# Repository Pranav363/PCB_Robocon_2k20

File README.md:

# PCB_Robocon_2k20
The ABU Asia-Pacific Robot Contest (ABU Robocon) is an Asian-Oceanian college robot competition.
In the competition, robots compete to complete a task within a set period of time.

Attached files are PCB designs used by TEAM VULCANS in Robocon2020 competition.
This repository contains .brd & .sch file desgined in EAGLE software.

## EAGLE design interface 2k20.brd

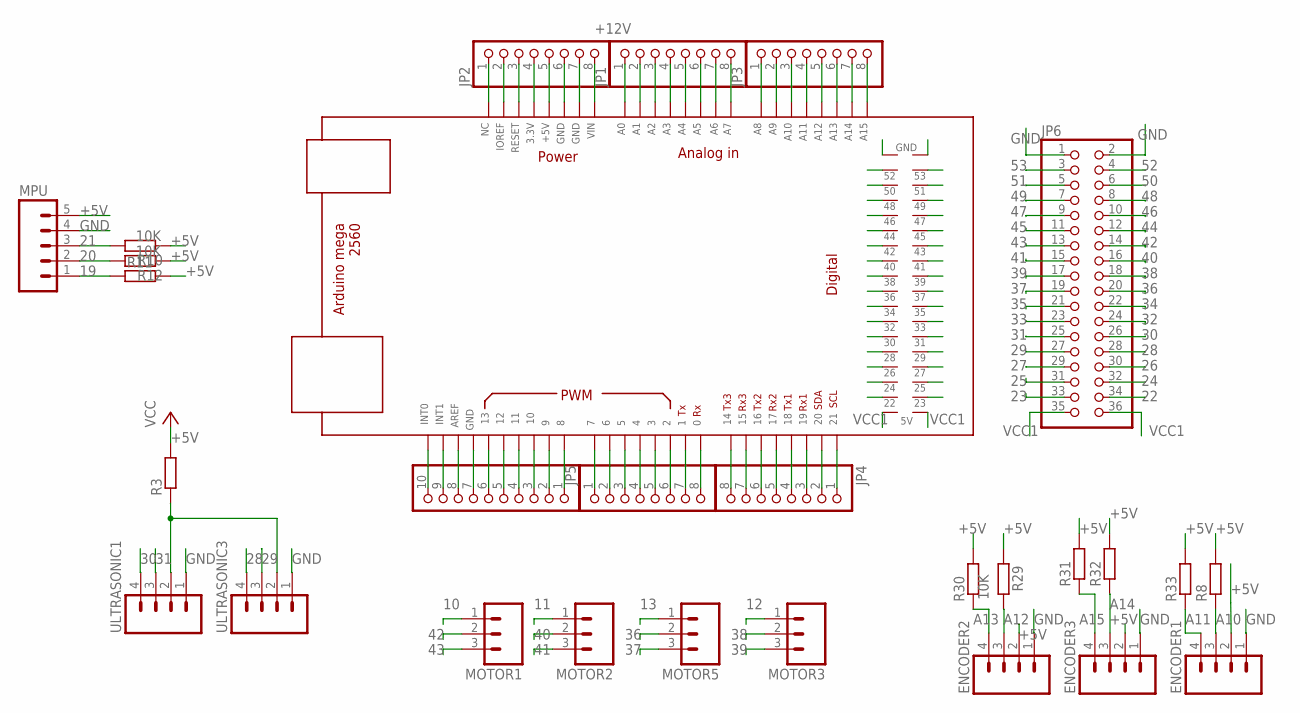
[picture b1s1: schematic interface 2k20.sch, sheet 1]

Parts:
ENCODER1, ENCODER2, ENCODER3: ULTRASONIC; MOLEX-1X4
JP1, JP2, JP3, JP4, JP5: PINHD-1X8; 1X08
JP6: PINHD-2X18; 2X18
MOTOR1, MOTOR2, MOTOR3, MOTOR5: M03POLAR; MOLEX-1X3@1
MPU: M05; 05P
PWMH1: pwm; 1X10
R3, R8, R11, R29, R31, R32, R33: R-EU_M0805; M0805
R10, R12, R30: 10K; M0805
U$1: MEGA_DEVICE; MEGABOX
ULTRASONIC1, ULTRASONIC3: ULTRASONIC; MOLEX-1X4

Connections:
0: JP5.8, U$1.0
1: JP5.7, U$1.1
2: JP5.6, U$1.2
3: JP5.5, U$1.3
3.3V: JP2.4, U$1.3V3
4: JP5.4, U$1.4
5: JP5.3, U$1.5
6: JP5.2, U$1.6
7: JP5.1, U$1.7
8: PWMH1.1, U$1.8
9: PWMH1.2, U$1.9
10: MOTOR1.1, PWMH1.3, U$1.10
11: MOTOR2.1, PWMH1.4, U$1.11
12: MOTOR3.1, PWMH1.5, U$1.12
13: MOTOR5.1, PWMH1.6, U$1.13
14: JP4.8, U$1.14
15: JP4.7, U$1.15
16: JP4.6, U$1.16
17: JP4.5, U$1.17
18: JP4.4, U$1.18
19: JP4.3, MPU.1, R11.2, U$1.19
20: JP4.2, MPU.2, R12.2, U$1.20
21: JP4.1, MPU.3, R10.2, U$1.21
22: JP6.34, U$1.22; also elsewhere on the board
23: JP6.33, U$1.23; also elsewhere on the board
24: JP6.32, U$1.24; also elsewhere on the board
25: JP6.31, U$1.25; also elsewhere on the board
26: JP6.30, U$1.26
27: JP6.29, U$1.27
28: JP6.28, U$1.28, ULTRASONIC3.4
29: JP6.27, U$1.29, ULTRASONIC3.3
30: JP6.26, U$1.30, ULTRASONIC1.4
31: JP6.25, U$1.31, ULTRASONIC1.3
32: JP6.24, U$1.32
33: JP6.23, U$1.33
34: JP6.22, U$1.34
35: JP6.21, U$1.35
36: JP6.20, MOTOR5.2, U$1.36
37: JP6.19, MOTOR5.3, U$1.37
38: JP6.18, MOTOR3.2, U$1.38
39: JP6.17, MOTOR3.3, U$1.39
40: JP6.16, MOTOR2.2, U$1.40
41: JP6.15, MOTOR2.3, U$1.41
42: JP6.14, MOTOR1.2, U$1.42
43: JP6.13, MOTOR1.3, U$1.43
44: JP6.12, U$1.44
45: JP6.11, U$1.45; also elsewhere on the board
46: JP6.10, U$1.46; also elsewhere on the board
47: JP6.9, U$1.47; also elsewhere on the board
48: JP6.8, U$1.48; also elsewhere on the board
49: JP6.7, U$1.49; also elsewhere on the board
50: JP6.6, U$1.50; also elsewhere on the board
51: JP6.5, U$1.51; also elsewhere on the board
52: JP6.4, U$1.52; also elsewhere on the board
53: JP6.3, U$1.53; also elsewhere on the board
+5V: ENCODER1.2, ENCODER2.2, ENCODER3.2, MPU.5, R3.2, R8.2, R10.1, R11.1, R12.1, R29.2, R30.2, R31.2, R32.2, R33.2; also elsewhere on the board
+12V: JP2.8, U$1.VIN; also elsewhere on the board
A0: JP1.1, U$1.A0
A1: JP1.2, U$1.A1
A2: JP1.3, U$1.A2
A3: JP1.4, U$1.A3
A4: JP1.5, U$1.A4
A5: JP1.6, U$1.A5
A6: JP1.7, U$1.A6
A7: JP1.8, U$1.A7
A8: JP3.1, U$1.A8
A9: JP3.2, U$1.A9
A10: ENCODER1.3, JP3.3, R8.1, U$1.A10
A11: ENCODER1.4, JP3.4, R33.1, U$1.A11
A12: ENCODER2.3, JP3.5, R29.1, U$1.A12
A13: ENCODER2.4, JP3.6, R30.1, U$1.A13
A14: ENCODER3.3, JP3.7, R32.1, U$1.A14
A15: ENCODER3.4, JP3.8, R31.1, U$1.A15
AREF: PWMH1.8, U$1.AREF
GND: ENCODER1.1, ENCODER2.1, ENCODER3.1, JP2.6, JP2.7, JP6.1, JP6.2, MPU.4, PWMH1.7, U$1.GND@1 (GND), U$1.GND@2 (GND), U$1.GND@3 (GND), U$1.GND@4 (GND), U$1.GND@5 (GND), ULTRASONIC1.1, ULTRASONIC3.1; also elsewhere on the board
INT0: PWMH1.10, U$1.INT2
INT1: PWMH1.9, U$1.INT1
IOREF: JP2.2, U$1.IOREF
unnamed: R3.1, ULTRASONIC1.2, ULTRASONIC3.2
NC: JP2.1, U$1.NC
RESET: JP2.3, U$1.RESET; also elsewhere on the board
VCC: JP2.5, U$1.5V; also elsewhere on the board
VCC1: JP6.35, JP6.36, U$1.5V@1 (5V), U$1.5V@2 (5V)

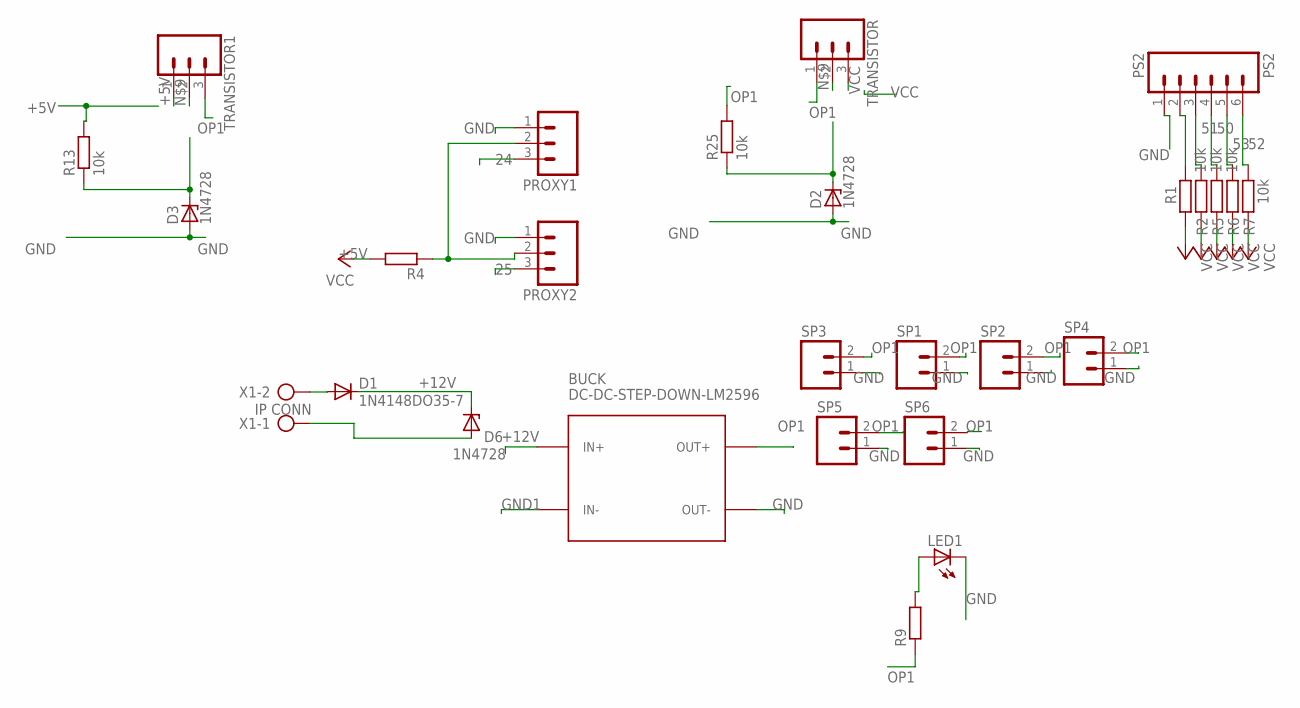
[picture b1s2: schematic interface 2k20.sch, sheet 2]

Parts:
BUCK: DC-DC-STEP-DOWN-LM2596
D1: 1N4148DO35-7; DO35-7
D2, D3, D6: 1N4728; DO41Z10
LED1: LEDCHIPLED_0805; CHIPLED_0805
PROXY1, PROXY2: M03POLAR; MOLEX-1X3@1
PS2: PS2; MOLEX-1X6
R1, R4: R-EU_M0805; M0805
R2, R5, R6, R7, R13, R25: 10k; M0805
R9: 500; M0805
SP1, SP2, SP3, SP4, SP5, SP6: M02; 02P
TRANSISTOR, TRANSISTOR1: CONN_03LOCK; 1X03_LOCK
X1: IP CONN; AK300/2

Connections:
24: PROXY1.3; also elsewhere on the board
25: PROXY2.3; also elsewhere on the board
50: PS2.4, R5.2; also elsewhere on the board
51: PS2.3, R2.2; also elsewhere on the board
52: PS2.6, R7.2; also elsewhere on the board
53: PS2.5, R6.2; also elsewhere on the board
+5V: R1.1, R2.1, R4.2, R5.1, R6.1, R7.1, R13.2, TRANSISTOR1.1; also elsewhere on the board
+12V: BUCK.IN+, D1.C, D6.C; also elsewhere on the board
GND: BUCK.OUT-, D2.A, D3.A, LED1.C, PROXY1.1, PROXY2.1, PS2.1, SP1.1, SP2.1, SP3.1, SP4.1, SP5.1, SP6.1; also elsewhere on the board
GND1: BUCK.IN-, D6.A, X1.1
unnamed: LED1.A, R9.2
unnamed: D1.A, X1.2
unnamed: PROXY1.2, PROXY2.2, R4.1
unnamed: D2.C, D3.C, R13.1, R25.1, TRANSISTOR.2, TRANSISTOR1.2
unnamed: PS2.2, R1.2
OP1: BUCK.OUT+, R9.1, R25.2, SP1.2, SP2.2, SP3.2, SP4.2, SP5.2, SP6.2, TRANSISTOR.1, TRANSISTOR1.3
VCC: TRANSISTOR.3; also elsewhere on the board

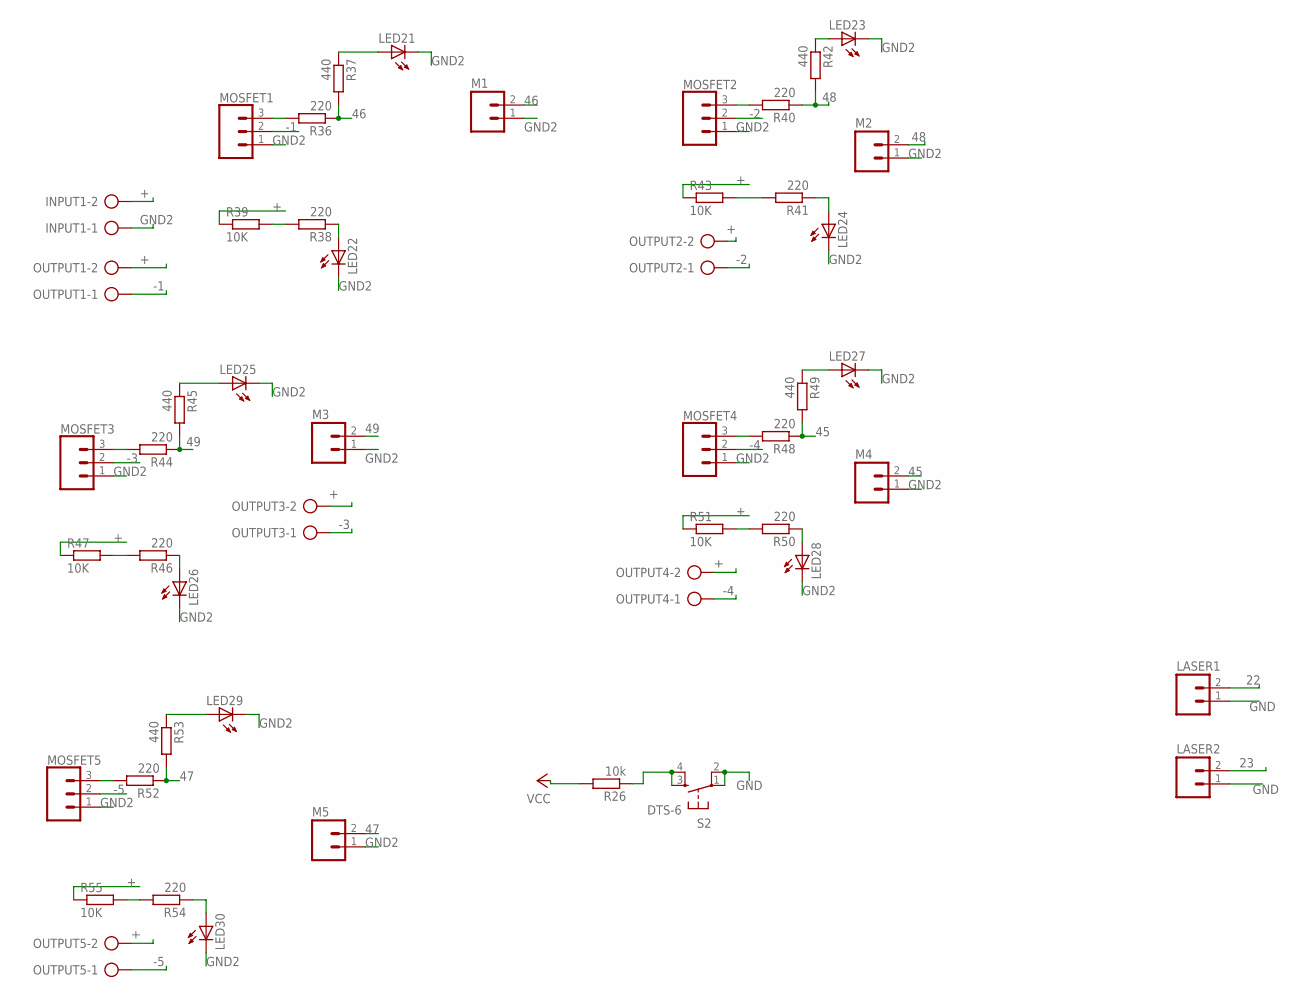
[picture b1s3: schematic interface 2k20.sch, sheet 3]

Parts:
INPUT1: AK300/2
LASER1, LASER2: M02; 02P
LED21, LED22, LED23, LED24, LED25, LED26, LED27, LED28, LED29, LED30: LEDCHIPLED_0805; CHIPLED_0805
M1, M2, M3, M4, M5: M02; 02P
MOSFET1, MOSFET2, MOSFET3, MOSFET4, MOSFET5: CONN_03LOCK; 1X03_LOCK
OUTPUT1, OUTPUT2, OUTPUT3, OUTPUT4, OUTPUT5: AK300/2
R26: 10k; M0805
R36, R38, R40, R41, R44, R46, R48, R50, R52, R54: 220; M0805
R37, R42, R45, R49, R53: 440; M0805
R39, R43, R47, R51, R55: 10K; R0805
S2: DTS-6

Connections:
22: LASER1.2; also elsewhere on the board
23: LASER2.2; also elsewhere on the board
45: M4.2, R48.1, R49.2; also elsewhere on the board
46: M1.2, R36.1, R37.2; also elsewhere on the board
47: M5.2, R52.1, R53.2; also elsewhere on the board
48: M2.2, R40.1, R42.2; also elsewhere on the board
49: M3.2, R44.1, R45.2; also elsewhere on the board
+: INPUT1.2, OUTPUT1.2, OUTPUT2.2, OUTPUT3.2, OUTPUT4.2, OUTPUT5.2, R39.1, R43.1, R47.1, R51.1, R55.1
+5V: R26.2; also elsewhere on the board
-1: MOSFET1.2, OUTPUT1.1
-2: MOSFET2.2, OUTPUT2.1
-3: MOSFET3.2, OUTPUT3.1
-4: MOSFET4.2, OUTPUT4.1
-5: MOSFET5.2, OUTPUT5.1
GND: LASER1.1, LASER2.1, S2.1, S2.2; also elsewhere on the board
GND2: INPUT1.1, LED21.C, LED22.C, LED23.C, LED24.C, LED25.C, LED26.C, LED27.C, LED28.C, LED29.C, LED30.C, M1.1, M2.1, M3.1, M4.1, M5.1, MOSFET1.1, MOSFET2.1, MOSFET3.1, MOSFET4.1, MOSFET5.1
unnamed: MOSFET1.3, R36.2
unnamed: LED21.A, R37.1
unnamed: LED22.A, R38.1
unnamed: R38.2, R39.2
unnamed: MOSFET2.3, R40.2
unnamed: LED23.A, R42.1
unnamed: R41.2, R43.2
unnamed: LED24.A, R41.1
unnamed: MOSFET3.3, R44.2
unnamed: LED25.A, R45.1
unnamed: LED26.A, R46.1
unnamed: R46.2, R47.2
unnamed: MOSFET4.3, R48.2
unnamed: LED27.A, R49.1
unnamed: LED28.A, R50.1
unnamed: R50.2, R51.2
unnamed: LED29.A, R53.1
unnamed: MOSFET5.3, R52.2
unnamed: R54.2, R55.2
unnamed: LED30.A, R54.1
RESET: R26.1, S2.3, S2.4; also elsewhere on the board

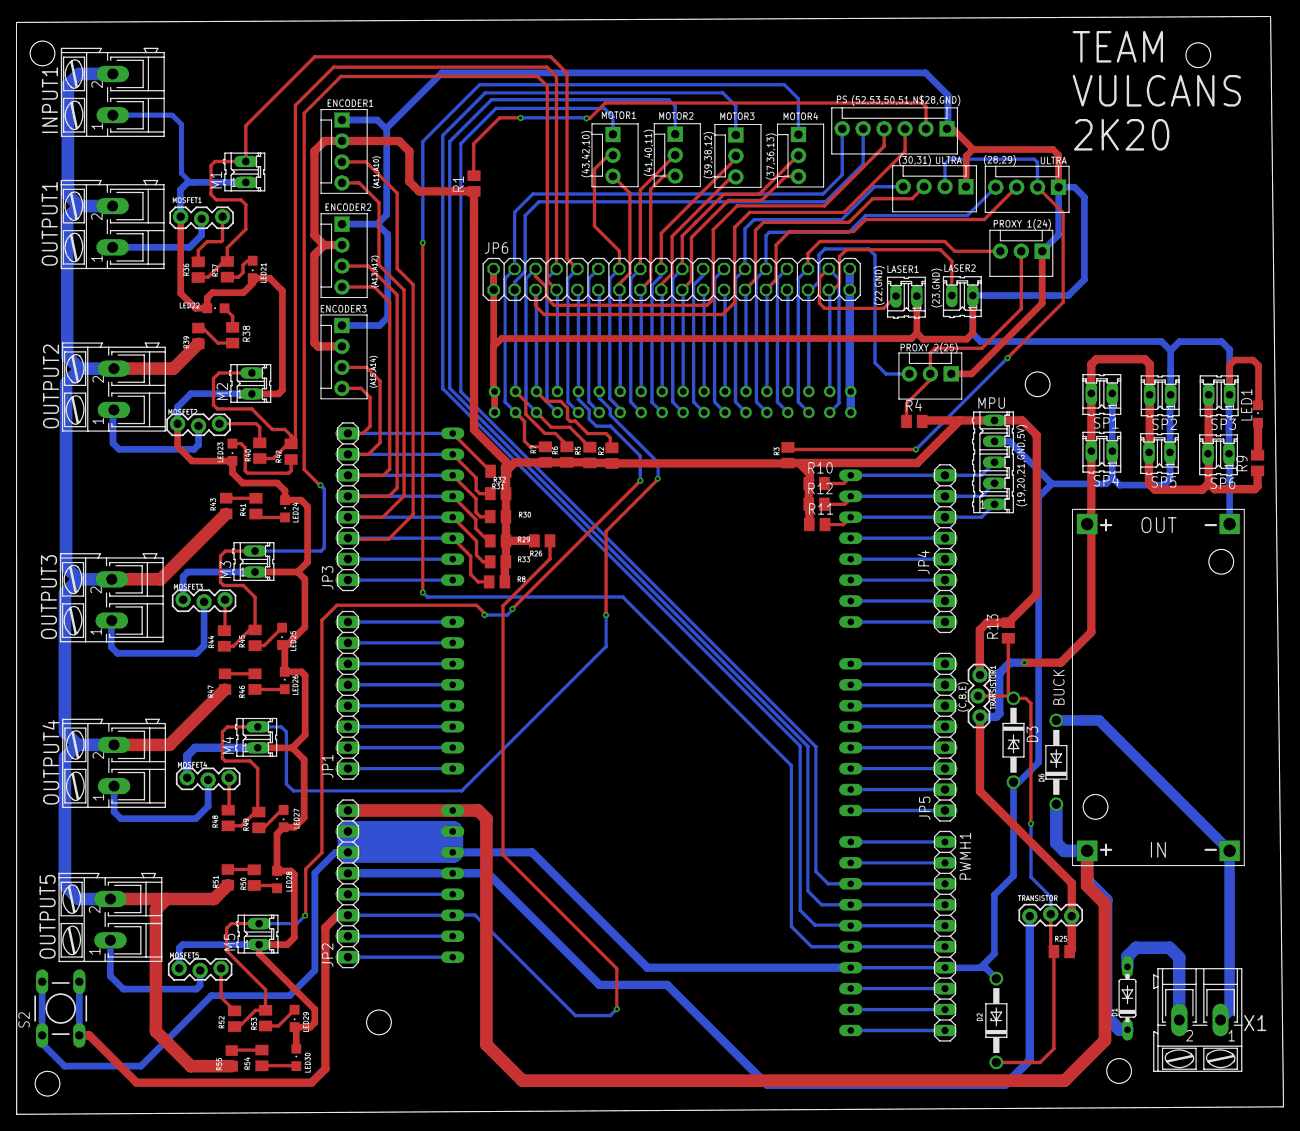
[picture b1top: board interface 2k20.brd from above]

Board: 2 copper layers, 153.6 x 133.1 mm, 105 parts (1 on the bottom side), 117 nets.

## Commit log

2023-09-01 Add files via upload
    Successfully Uploaded.

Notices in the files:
parts and their libraries:
SparkFun-Connectors: Licensing: Creative Commons ShareAlike 4.0 International - https://creativecommons.org/licenses/by-sa/4.0
diy-modules: Released under the Creative Commons Attribution 4.0 International License: http://creativecommons.org/licenses/by/4.0
